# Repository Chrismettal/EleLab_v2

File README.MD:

# Elelab_v2 <!-- omit in toc -->

## Table of contents <!-- omit in toc -->

- [Buying](#buying)
- [The concept](#the-concept)
- [The PCBs](#the-pcbs)
  - [Bus100 / Bus150](#bus100--bus150)
  - [PowerFeed](#powerfeed)
  - [Frontpanel\_a](#frontpanel_a)
- [The modules](#the-modules)
  - [Supplies](#supplies)
  - [Supply from ATX/SFX](#supply-from-atxsfx)
  - [Supply from XT60/Barrel](#supply-from-xt60barrel)
  - [Supply from Meanwell PSU](#supply-from-meanwell-psu)
  - [Supply from Bosch 18 V Battery](#supply-from-bosch-18-v-battery)
  - [Lab PSU fixed](#lab-psu-fixed)
  - [Lab PSU variable](#lab-psu-variable)
  - [Oscilloscope DSO138](#oscilloscope-dso138)
  - [Resistor decade](#resistor-decade)
    - [Performance](#performance)
  - [Component tester](#component-tester)
  - [Raspberry Pi](#raspberry-pi)
  - [Display](#display)
  - [Electronic Load](#electronic-load)
  - [Signal generator](#signal-generator)
  - [Audio amplifier / signal tracer](#audio-amplifier--signal-tracer)
  - [TS100 Soldering station](#ts100-soldering-station)
- [Tips and tricks](#tips-and-tricks)

This is a low cost, modular elctronics lab system for hobbyists.
The customizable modules include fixed and variable power supplies, measurement tools, component testers and much more.
Everything in here is done with open source software, including FreeCAD for all the 3d printable files and KiCAD for the PCBs.
I have made a set of modules already and am in the process of creating many more. Raw PCB project files, Gerbers and FreeCAD projects are all uploaded here for your customizing needs, while the finished modules are uploaded to Prusaprinters. Please be sure to upload any remix you do as it might be useful for others and especially myself!

The system features a set of backpanel bus PCBs as well as panel breakout PCBs. While the backpanel bus is not neccesary, it keeps the system modular, hot swappable and tidy. You can have the gerbers manufactured for cheap at your favorite chinese PCB house or just shoot me a message. I might have spares.

Finished modules for printing yourself for any module can be found [here in the Prusaprinters collection](https://www.prusaprinters.org/social/13425-chrismettal/collections/14323).
For most of the modules a printbed of 160x160mm and 175mm of height is sufficient, but the ATX and SFX module require print bed sizes of up to 250mm width (Prusa MK2 and up dimensions). I printed all of the modules in PLA and just to speed things up i used a 0.6mm nozzle but that is not required at all.

**If you like my work please consider [supporting my caffeine addiction](https://gitlab.com/Chrismettal#donations)!**

## Buying

All PCBs as well as 3D printed parts are now stocked at Tindie!

## The concept

The system consists of 3 basic sizes of modules, 100mm, 150mm and 200mm. For the 100mm and the 150mm frame there is a backpanel bus that interconnects the modules together for power delivery. The 200mm frame uses two of the 100mm PCBs.

For the modules we usually use one of the 3 base sizes and punch holes in the upper and/or lower front panel to suit our mounting needs. This can be done in FreeCAD by modifying the BaseXXX file or a finished module that best fits your new module. Alternatively you can also just edit the .stl files in the editor of your choice.

The backpanel bus is equipped to transfer 24 V, 12 V and 5 V (and GND, duh), which we feed into the system by one of the "Supply" modules. At the moment i made an SFX-PSU supply module (supplying 12 V and 5 V) and one with a 5.5mm barrel jack and XT60 jack (Using 24 V supplies and step-down converters for 12 V and 5 V). Both of these supply modules feature the PowerFeed PCB to feed into the backpanel bus. Because 24 V is rarely needed for most of the modules, the easiest and safest way to use this system is the SFX module, which just plugs into the PowerFeed PCB.

Obviously you can just run wires between the modules and omit the backpanel bus, but it will probably make me a little sad.

If you are using the bus, individual modules just plug into each other to form a single unit. 

With 2 little printed clips you can secure the modules together so they don't seperate during the occasional earthquake or lab-ragequit.

Almost none of the 3d printable pieces require supports. The frame of each module has integrated supports at one position, that you will need to cut away after printing:

## The PCBs

All of the PCBs can be cheaply manufactured in China (trust me, it's easier and cheaper than you think) or sometimes i even have spares left, if you shoot me a message.

### Bus100 / Bus150

This is the basic backpanel bus to link individual modules together. Though optional, it greatly enhances your experience in building this system.

**Parts:**

- 2pcs 2.54mm Pinheader right angle 2x8 female
- 2pcs 2.54mm Pinheader right angle 2x8 male

### PowerFeed

This is the main infeed to connect your power supply to the backpanel bus and feed into the modules. It packs jacks to plug in your SFX supply, screw connectors for external fuses, and a breakout for the SFXs standby switch. Alternatively you could wire up your supplies directly to the spots marked as 24V, 12V and 5V respectively without using ATX connectors.

Using a PC supply, 12 V are supplied through either a 4 or 8 pin CPU header power plug. You cannot use the 8-pin GPU plug on your high end ATX PSU.

**Parts:**

- 24 Pin 4.2mm ATX Connector standing 
-  8 Pin 4.2mm ATX Connector standing
- 6pcs 5.08mm 2 Pin screw terminal (The blue cheap ones, optional though)

### Frontpanel_a

Here we have the basic front panel breakout with industry style screw-plug connectors and USB jacks. The USB Jacks have a 0805 footprint in line with the 5 V rail so you can optionally install a tiny polyfuse in there. The data lines of each USB port are broken out so you can either use it for normal data transfer, or do whatever the best quick charge port configuration on the data lines is today. (for example bridging D+ and D- to put old Android phones into quick charge mode)

**Parts:**

- 2pcs 5.08mm pcb screw terminal block 4 pin
- 2pcs standing vertical USB Ports
- 2pcs 0805 polyfuse 1.1A (Or your desired amperage)

## The modules

### Supplies

No matter what Infeed you use, you should aim for around 100 - 150 W of power in general. I use a 24 V,  150 W power supply to infeed into my system. For PC supplies you should watch for the individual rail current, as a PSU might show 5 A of 12 V, but split over 5 rails, so if you only use one rail you will only get 1 A out of your PSU.

### Supply from ATX/SFX

The easiest way to supply power to your EleLab is to use a regular ATX or SFX computer power supply. Using the PowerFeed PCB you can plug in the 24pin and 8pin connectors of your PSU directly into the backpanel bus. The module is preconfigured to use fuses for the 12 V and 5 V rails. You could install a switch for the PowerON PSU signal but i usually just bridge it completely so i switch the EleLab on and off by the main power switch on the back of the PSU.

Make sure the fan of your PSU is exposed as in the picture as not to overheat your poor PSU.

In the picture you see me build the SFX version of the module, the ATX version is printing at the time of writing this and is not tested yet.

**Parts:**

- PowerFeed PCB
- 2pcs screw in fuse holder panel mount
- SFX PSU of your choice
- 5pcs M2x8 self tapping screws

### Supply from XT60/Barrel

With this supply module you can use any external 12 V or 24 V Power supply you want. You could even plug in some batteries with the XT60 jack!
This module however needs some beefy DC-DC step-down converters to create the 5 V rail, as well as the 12 V rail if you are using a 24 V supply. 
There is a printable tray that just snaps into the bottom, capable of carrying two of these types of step down converters:

These are readily available from china for a few bucks if you search for "step-down XL4016" on ebay. XL4016 is the name of the IC but it's the closest to a part number we get.

One of the converters will be set to output 5 V and one to output 12 V, when you supply the module with 24 V DC. This will give you all 3 voltages on the backpanel bus. The modules can also be configured for current limiting, which I set to 2 A each.

**Parts:**

- PowerFeed PCB
- 3pcs screw in fuse holder panel mount
- 2pcs DC-DC Step down converters XL4016
- 9pcs M2x8 self tapping screws

### Supply from Meanwell PSU

Using the same step down converters, but this time using an internal PSU, the Meanwell module directly integrates a high quality supply into your EleLab. 
Since you will need to wire up mains voltage i can NOT show you how to do this. 
The Module uses an IEC C14 plug with integrated switch and fuse. Can't really find an exact name to google for.

The Meanwell supply should be a 24 V one, preferably the 150 W model, using the step down converters to step the voltage to 12 V and 5 V respectively.

**Parts:**

- PowerFeed PCB
- 3pcs screw in fuse holder panel mount
- 2pcs DC-DC Step down converters XL4016
- 9pcs M2x8 self tapping screws
- 4pcs M3x5 metric screws
- Meanwell RS-150-24
- IEC C14 Plug with switch and fuse

### Supply from Bosch 18 V Battery

With this module you can use your 18 V Bosch batteries to supply a portable lab system. It also uses the same step down converters for rails of 18 V - 12 V and 5 V. Additionaly you will need two locking blade edge connectors. These are widely used in the car industry for confectionable plugs. The part number I found was “8KW048056-033” for a 6.3mm blade with 2.5mm² wire capacity.

Please note that 18 V Bosch batteries do NOT have over discharge protection built into the pack and can take damage if you run them below their specified "empty" point! Always watch the meter on your battery and make sure to use them in a healthy range. 

The edge connectors are slid in from the inside of the case and lock into place.

**Hint:** see also [standalone version](https://www.prusaprinters.org/prints/109595-bosch-18-v-battery-powerbank-power-supply)

**Parts:**

- PowerFeed PCB
- 3pcs screw in fuse holder panel mount
- 2pcs DC-DC Step down converters XL4016
- 9pcs M2x8 self tapping screws
- 2pcs “8KW048056-033” connectors
- Bosch 18 V battery

### Lab PSU fixed

The first actually usable module is a power breakout for your 5 V, 12 V and optionally 24 V rails. Using cheap chinese banana jacks with 12mm OD all rails can be accessed. In the front we use the Frontpanel_a PCB to have connections beside the banana jacks. Which terminal you connect to which rail is only dependend on your preferences. Obviously make sure to not reverse polarity on the USB ports or risk frying something. 

Here you can see the spagetthi wiring behind mine:

Be sure to bend over your connectors as seen here as there is not extremely much room for the upper front panel to slide down:

The banana jacks are intentionally uncentered to make room for labeling on the left. I did not have time to create printable labels yet but i will get to it.

**Parts:**

- 12 or 18pcs banana jacks
- Bus100 PCB
- Frontpanel_a PCB
- 10pcs M2x8 self tapping screws

### Lab PSU variable

Similar to the fixed supply we use a Frontpanel_a PCB here. The two variable step down converters (ebay is your friend again, TBDnameOfStepDown) are fed by either the 24 V or 12 V rail, depending on your infeed capabilities. Under each converter i put two banana jacks as the output, but also in parallel i wire up the industrial screw-plug connectors in the front to be outputs as well. If you are feeling adventurous you can also but the USBs behind the converters, but be vary that you can potentially but up to 24 V through the USB port then if you tell the converter to do it. The USB Jack will not be a happy charging port but rather something for debugging.

**Parts:**

- 2pcs DPS30005 or similar step down converter. You can get these in all voltage ranges under different names.
- 4pcs banana jacks
- Bus100 PCB
- Frontpanel_a PCB
- 10pcs M2x8 self tapping screws

### Oscilloscope DSO138

The DSO138 is a great "Babies first oscilloscope". This super cheap thing is awesome if you don't wanna shell out serious cash if you are going to look at simple waveforms once per year and don't really care about accuracy a lot. Oftentimes i just wanna know IF something is even executing code and don't care HOW it is doing it so i often still fire up the DSO138.

You have to remove the old power jack of the DSO138 PCB and feed in power through a 13mmx19mm rocker switch out of the 12 V rail for this to fit. 4 x M3 screws with nuts fix the DSO PCB into the panel from the back. The BNC jack is also removed, a new frontpanel screw-in BNC jack is installed in the front, and wired up to where the original jack was. This is best done with a shielded cable (though i doubt you will see much difference with a DSO of this quality..)

**Parts:**

- DSO138 kit
- 12mmx19mm rocker switch
- Bus150 PCB
- 4pcs M3 screws and nuts
- 6pcs M2x8 self tapping screws

### Resistor decade

Not really needing a backpanel this can safely be placed as the last piece of the EleLab as it does not even require power. Please follow your favorite guide on how to wire up your decade.

The 2 ends of the resistor decade are wired to two banana jacks. Also i installed 2 potentiometers into the panel, giving me some more flexibility. These are also just wired straight into 3 banana connectors.

Closing this module is tricky as well. You will need to NOT snap in the decade before sliding the front panel down:

A [schematic on how to wire the KSA-2 switches](PCB_CAD/EleLab_v2_RDecSchematic/RDecSchematic/RDecSchematic.pdf) is provided in [PDF](PCB_CAD/EleLab_v2_RDecSchematic/RDecSchematic/RDecSchematic.pdf) form, as well as a [KiCAD project](PCB_CAD/EleLab_v2_RDecSchematic/../../PCB_CAD/EleLab_v2_RDecSchematic/RDecSchematic/RDecSchematic.kicad_pro).

#### Performance

The high number of switch contacts will  cause a significant resistance error in the low range of `0-100R`, but for values above `100R` the accuracy raises greatly. The bad performance of the lower values skews the full range average / median, so seperate values for different ranges are provided.

| Range      | Average Error % | Median Error % |
| ---------- | --------------- | -------------- |
| 1R - 100R  | 16.697          | 9.890          |
| 100R - 10M | -0.265          | -0.395         |
| Full range | 16.697          | 9.890          |

These raw values have been recorded with a Keysight 34461A using 4-Wire resistance measurement:

| Target [R]  | Actual [R]  | Error [R]  | Error [%] |
| ----------- | ----------- | ---------- | --------- |
| 1.000       | 2.044       | 1.044      | 104.400   |
| 2.000       | 3.016       | 1.016      | 50.800    |
| 3.000       | 4.036       | 1.036      | 34.533    |
| 4.000       | 4.992       | 0.992      | 24.800    |
| 5.000       | 5.985       | 0.985      | 19.700    |
| 6.000       | 6.986       | 0.986      | 16.433    |
| 7.000       | 7.990       | 0.990      | 14.143    |
| 8.000       | 9.024       | 1.024      | 12.800    |
| 9.000       | 10.063      | 1.063      | 11.811    |
| 10.000      | 10.989      | 0.989      | 9.890     |
| 20.000      | 20.995      | 0.995      | 4.975     |
| 30.000      | 30.974      | 0.974      | 3.247     |
| 40.000      | 40.937      | 0.937      | 2.342     |
| 50.000      | 50.910      | 0.910      | 1.820     |
| 60.000      | 60.910      | 0.910      | 1.517     |
| 70.000      | 70.869      | 0.869      | 1.241     |
| 80.000      | 80.774      | 0.774      | 0.968     |
| 90.000      | 90.730      | 0.730      | 0.811     |
| 100.000     | 101.004     | 1.004      | 1.004     |
| 200.000     | 200.762     | 0.762      | 0.381     |
| 300.000     | 300.620     | 0.620      | 0.207     |
| 400.000     | 400.670     | 0.670      | 0.168     |
| 500.000     | 500.468     | 0.468      | 0.094     |
| 600.000     | 600.120     | 0.120      | 0.020     |
| 700.000     | 699.932     | -0.068     | -0.010    |
| 800.000     | 799.801     | -0.199     | -0.025    |
| 900.000     | 899.823     | -0.177     | -0.020    |
| 1000.000    | 999.342     | -0.658     | -0.066    |
| 2000.000    | 2000.430    | 0.430      | 0.022     |
| 3000.000    | 2998.200    | -1.800     | -0.060    |
| 4000.000    | 3999.820    | -0.180     | -0.004    |
| 5000.000    | 4998.400    | -1.600     | -0.032    |
| 6000.000    | 5998.460    | -1.540     | -0.026    |
| 7000.000    | 6996.200    | -3.800     | -0.054    |
| 8000.000    | 7993.540    | -6.460     | -0.081    |
| 9000.000    | 8991.460    | -8.540     | -0.095    |
| 10000.000   | 9957.250    | -42.750    | -0.428    |
| 20000.000   | 19904.500   | -95.500    | -0.478    |
| 30000.000   | 29845.600   | -154.400   | -0.515    |
| 40000.000   | 39806.000   | -194.000   | -0.485    |
| 50000.000   | 49754.000   | -246.000   | -0.492    |
| 60000.000   | 59723.000   | -277.000   | -0.462    |
| 70000.000   | 69684.700   | -315.300   | -0.450    |
| 80000.000   | 79651.800   | -348.200   | -0.435    |
| 90000.000   | 89589.100   | -410.900   | -0.457    |
| 100000.000  | 99555.100   | -444.900   | -0.445    |
| 200000.000  | 199155.000  | -845.000   | -0.423    |
| 300000.000  | 298855.000  | -1145.000  | -0.382    |
| 400000.000  | 398422.000  | -1578.000  | -0.395    |
| 500000.000  | 498035.000  | -1965.000  | -0.393    |
| 600000.000  | 597631.000  | -2369.000  | -0.395    |
| 700000.000  | 697278.000  | -2722.000  | -0.389    |
| 800000.000  | 796824.000  | -3176.000  | -0.397    |
| 900000.000  | 896647.000  | -3353.000  | -0.373    |
| 1000000.000 | 993580.000  | -6420.000  | -0.642    |
| 2000000.000 | 1987110.000 | -12890.000 | -0.645    |
| 3000000.000 | 2979190.000 | -20810.000 | -0.694    |
| 4000000.000 | 3974220.000 | -25780.000 | -0.645    |
| 5000000.000 | 4970280.000 | -29720.000 | -0.594    |
| 6000000.000 | 5965340.000 | -34660.000 | -0.578    |
| 7000000.000 | 6958820.000 | -41180.000 | -0.588    |
| 8000000.000 | 7953500.000 | -46500.000 | -0.581    |
| 9000000.000 | 8948330.000 | -51670.000 | -0.574    |
| 9999999.000 | 9944400.000 | -55599.000 | -0.556    |

**Parts:**

- 7pcs Thumbwheel switches KSA-2 with the ending caps
- 9pcs each of 1, 10, 100, 1k, 10k, 100k and 1M Ohm reistor
- 2pcs 9mm potentiometers of your choice, i used 5K B and 25K B
- 8pcs banana jacks
- Bus100 PCB
- 4pcs M2x8 self tapping screws

### Component tester

You would not believe how much utility you will get out of these things. They are also very cheaply ordered from ebay, screw into the upper panel from the backside and can identify almost all of the components you throw at it. Usually these are fed by a 9 V battery and while you could till do that and have a battery lying inside the module i just feed it from the 12 V rail. Don't know about any longterm damages though.

I wired 3 banana jacks right to the easiest to reach points numbered 1, 2 and 3.

**Parts:**

- Component Tester module
- 3pcs banana jacks
- Bus100 PCB
- 9pcs M2x8 self tapping screws

### Raspberry Pi 

Raspberry Pi carrier with USB / Ethernet / HDMI and GPIO broken out, including HAT compatible front plate. I use a "GPIO screw terminal hat" as the front plate to easily break out all GPIOs, but still be able to connect a GPIO extension cord down to a breadboard, or stack more HATs on top.

The Pi is powered through the bottom side of the GPIO header since the top side is taken by the GPIO extension cord. 5 V from the back panel is directly applied through a rocker switch.

Make sure to plug in the GPIO extension as shown. This is basically the only way it will be long enough and also the only way where the new header in the upper panel will be right side up and not mirrored.
I recommend mounting a breakout / extension HAT as shown to have easy screw terminal access to all GPIO pins, but still be able to plug HATs on top of it. Mounting the HAT now, screwing in PCB standoffs and THEN hot-snotting the extension cord in place from the back makes mounting much easier.

You will also need an angled mini-HDMI to HDMI cable. Make sure it is angled the correct way since it won't fit otherwise.

**Parts:**

- Raspberry Pi
- HDMI Female - Female front panel connector
- GPIO extension cord male-female about 150mm
- Bus100 PCB
- 12mmx19mm rocker switch
- angled short mini-HDMI to HDMI cable
- optionally - GPIO breakout board of your choice

### Display

7 Inch HDMI Display with touchscreen. HDMI and USB broken out.

**WARNING:** currently, to use the same frontpanel, a USB-A plug is used for the touchscreen. Usually you would use a Micro USB, USB C, or USB-B header for this breakout. To actually use the touchscreen for now you would have to use an USB-A to A cable, until someone made a frontpanel for USB-C or Micro USB (might be me idk).
If you are using the Frontpanel_A be sure to NOT populate the fuse, so you disconnect the 5 V rails of both USB devices.

You will need a short angled HDMI cable and an angled USB-Micro cable like shown, as straight cables won't fit in the frame. The HDMI cable connects directly to a female-female HDMI front panel mount, while the USB cable is cut open and soldered to the Frontpanel_A.

The display is powered with 5 V through a rocker switch, soldered directly to the shown points on the board. I used the GND of one of the Micro USB plugs, and 5 V is applied to the middle of the display switch. You could also cut open a second USB cable and use that, but I did not want to waste these precious angled cables

This modules works great in conjunction with the RPi module!

**Parts:**

- Waveshare 7 inch HDMI Display C
- 2 x Bus100 PCB
- Frontpanel_A PCB with only one USB jack mounted
- 12mmx19mm rocker switch
- 8pcs M2x8 self tapping screws
- 6pcs M3x15 metric screws with nuts
- female-female HDMI front panel connector
- angled HDMI cable
- angled micro USB cable

### Electronic Load

30 W electronic load module, don't know everything it can do yet, but you'll figure it out.
This module actually uses the fan opening in the back of the frame since it does generate some heat (duh).
It does have 4 wire measurement but I chose to omit this here to avoid confusion. For loads this small and modules with this low accuracy I did not see the benefit. The 4 wire measurement is therefore connected on the inside to the 2 terminals directly:

**Parts:**

- WEL3005 or similar electronic load module
- Bus100 PCB
- Frontpanel_A PCB
- 8pcs M2x8 self tapping screws
- 30mm fan

### Signal generator

4-20mA / 2-10 V / PWM signal generator. All contacts are broken out to banana jacks as well as the front panel in the order of your choice.

**Parts:**

- WSFG-06 or similar signal generator module
- Bus100 PCB
- Frontpanel_A PCB
- 8pcs M2x8 self tapping screws

### Audio amplifier / signal tracer

Mono speaker with tiny amplifier mainly for audible signal tracing. Music won't sound good on this device so please don't expect a workshop audio system in your lab. Left and right inputs are shorted together and the right input on the PAM is pulled to GND so we only use the left input in mixed-down-mono configuration.

The speaker is only glued in to accomodate all speaker sizes, so any speaker with below around 80mm diameter will work. 3-4 W is a typical power for speakers of these sizes.

Since this device is only mono, you should connect both channels together to one PAM input. For this, use two resistors (anything between 3k3 and 10k is probably fine) as shown here.

I put the output of both resistors to both channels so it does not matter which channel I use for the speaker output. I also put some heatshrink over the two resistors for some mechanical stability.

**Parts:**

- PAM8403 amplifier module with switching pot
- Bus100 PCB
- Some speaker - 75mm outer dia in my case
- 1/4 (6.35mm) Inch stereo jack

### TS100 Soldering station

Soldering "station" for TS100 soldering irons. The Iron can be kept in an ugly holder up top, powered by the XT60 plug below. The upper front plate is done with two snap-in buckets since the buckets are too deep to be sled in from the top fully. The upper bucket is meant for a soldering sponge and the lower bucket can keep your solder wire. I would either print the upper one in something heat resistant like PC or just use some aluminium tape on the inside so you don't burn the plastic with the hot tip.

The XT60 plug is snapped in from the front after soldering some heavy wires to it. Afterwards you can solder the wires to the Bus100 PCB (24V). 

The skateboard bearing is just pressed in the top. If it's too loose you can also glue it in.

Both buckets snap in from the front as the last item.

Make sure to use this module "more to the left" of your EleLab, since it draws quite a lot of power, which you probably don't want to travel through 20 modules.

**Parts:**

- Bus100 PCB
- 608ZZ skateboard bearing for the holder
- XT60 female plug

## Tips and tricks

You can keep the wires nice and short if you put together the modules as follows:

### Wire up your frontpanels  <!-- omit in toc -->

### If your wires are long enough you can place and screw in your backpanel bus already <!-- omit in toc -->

### Slide on the UPPER PANEL FIRST but don't do it all the way yet. <!-- omit in toc -->

### Slide in the LOWER PANEL now. You will see how this requires much less wiring you need for this. <!-- omit in toc -->

### Now slide on the upper panel fully. <!-- omit in toc -->

### If you have really short cables running from your front panels to your backpanel bus you can also slide in the frontpanel first and only then screw the backpanel bus into the frame. <!-- omit in toc -->

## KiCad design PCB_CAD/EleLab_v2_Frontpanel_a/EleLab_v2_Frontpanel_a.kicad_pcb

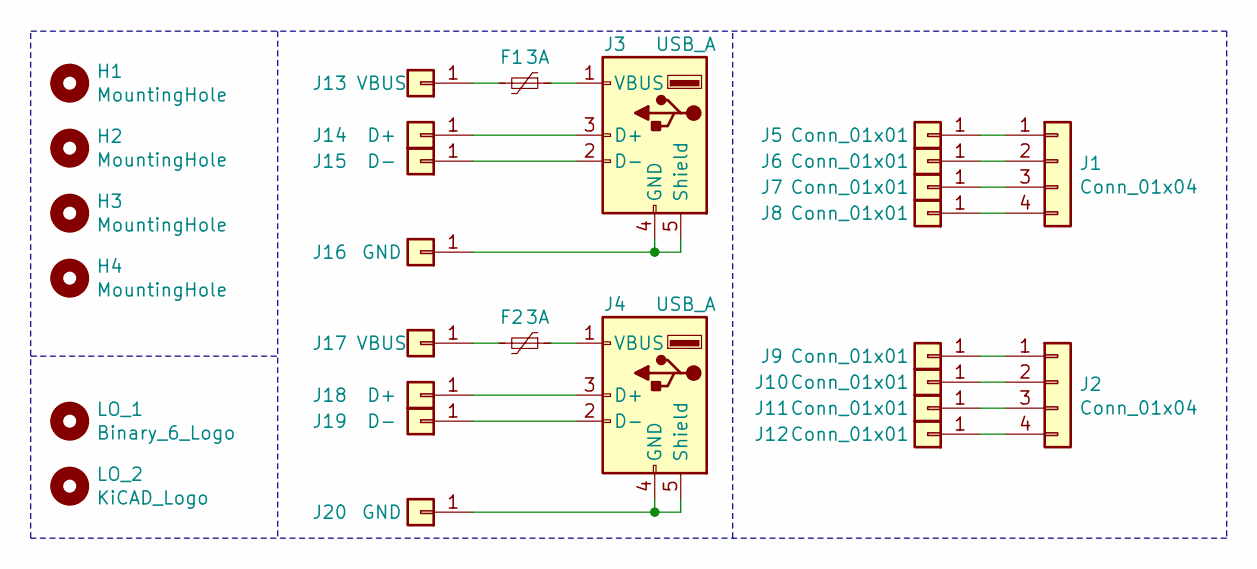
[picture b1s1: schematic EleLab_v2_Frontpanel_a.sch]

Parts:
F1, F2: 3A; Fuse_0805_2012Metric_Pad1.15x1.40mm_HandSolder
H1, H2, H3, H4: MountingHole; EigenesMountingHole_2.7mm_M2.5
J1, J2: Conn_01x04; PhoenixContact_MSTBA_2,5_4-G-5,08_1x04_P5.08mm_Horizontal
J3, J4: USB_A; USB_B_Standing
J5, J6, J7, J8, J9, J10, J11, J12: Conn_01x01; PinHeader_1x01_P2.54mm_Vertical
J13, J17: VBUS; PinHeader_1x01_P2.54mm_Vertical
J14, J18: D+; PinHeader_1x01_P2.54mm_Vertical
J15, J19: D-; PinHeader_1x01_P2.54mm_Vertical
J16, J20: GND; PinHeader_1x01_P2.54mm_Vertical
LO_1: Binary_6_Logo; Binary_6_v0.1
LO_2: KiCAD_Logo; Symbol_KiCAD-Logo_CopperAndSilkScreenTop

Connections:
unnamed: F1.1, J3.1 (VBUS)
unnamed: F1.2, J13.1
unnamed: F2.1, J4.1 (VBUS)
unnamed: F2.2, J17.1
unnamed: J1.1, J5.1
unnamed: J1.2, J6.1
unnamed: J1.3, J7.1
unnamed: J1.4, J8.1
unnamed: J2.1, J9.1
unnamed: J2.2, J10.1
unnamed: J2.3, J11.1
unnamed: J2.4, J12.1
unnamed: J3.3 (D+), J14.1
unnamed: J3.2 (D-), J15.1
unnamed: J3.4 (GND), J3.5 (Shield), J16.1
unnamed: J4.3 (D+), J18.1
unnamed: J4.2 (D-), J19.1
unnamed: J4.4 (GND), J4.5 (Shield), J20.1

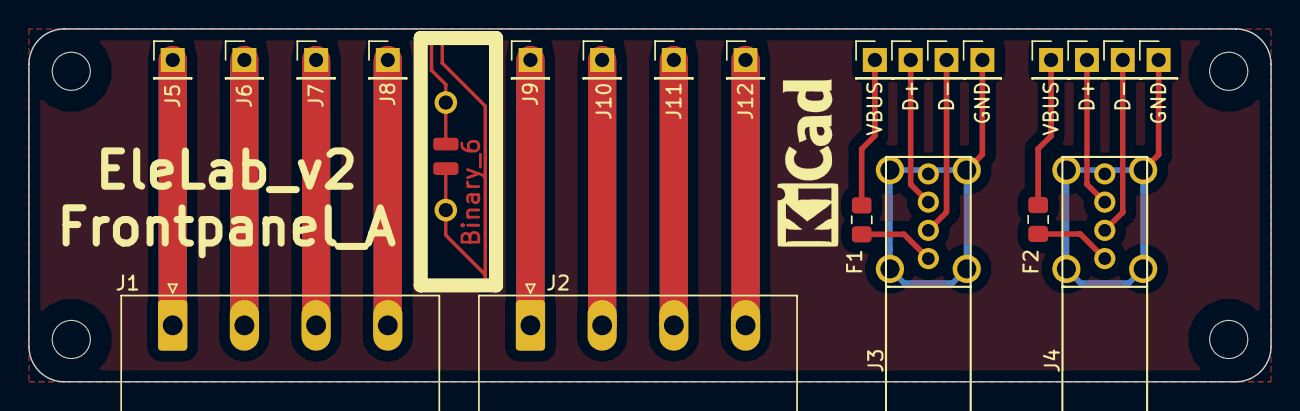
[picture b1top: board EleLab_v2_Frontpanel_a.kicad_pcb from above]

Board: 2 copper layers, 88.0 x 25.0 mm, 28 parts (0 on the bottom side), 18 nets.

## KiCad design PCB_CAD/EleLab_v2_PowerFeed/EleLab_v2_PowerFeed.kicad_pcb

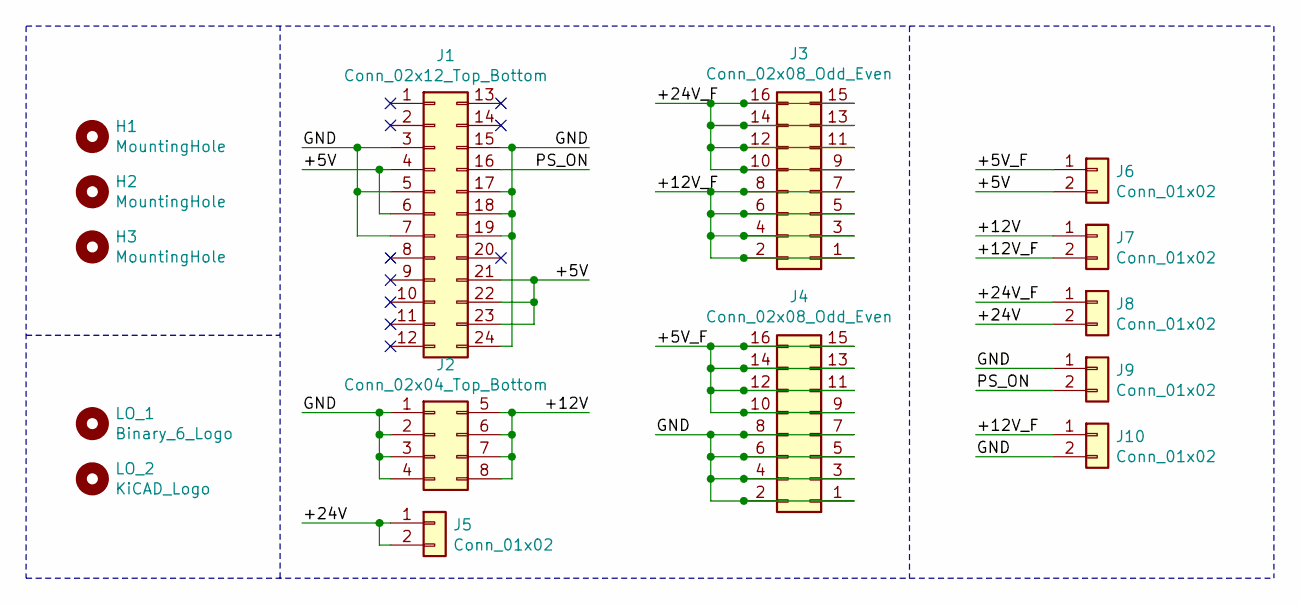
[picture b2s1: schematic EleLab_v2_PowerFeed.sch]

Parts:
H1, H2, H3: MountingHole; EigenesMountingHole_2.7mm_M2.5
J1: Conn_02x12_Top_Bottom; Molex_Mini-Fit_Jr_5566-24A_2x12_P4.20mm_Vertical
J2: Conn_02x04_Top_Bottom; Molex_Mini-Fit_Jr_5566-08A_2x04_P4.20mm_Vertical
J3, J4: Conn_02x08_Odd_Even; PinSocket_2x08_P2.54mm_Horizontal_NoSilk
J5, J6, J7, J8, J9, J10: Conn_01x02; TerminalBlock_bornier-2_P5.08mmNoSilk
LO_1: Binary_6_Logo; Binary_6_v0.1
LO_2: KiCAD_Logo; Symbol_KiCAD-Logo_CopperAndSilkScreenTop

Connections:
/+5V: J1.4, J1.6, J1.21, J1.22, J1.23, J6.2
/+5V_F: J4.9, J4.10, J4.11, J4.12, J4.13, J4.14, J4.15, J4.16, J6.1
/+12V: J2.5, J2.6, J2.7, J2.8, J7.1
/+12V_F: J3.1, J3.2, J3.3, J3.4, J3.5, J3.6, J3.7, J3.8, J7.2, J10.1
/+24V: J5.1, J5.2, J8.2
/+24V_F: J3.9, J3.10, J3.11, J3.12, J3.13, J3.14, J3.15, J3.16, J8.1
/GND: J1.3, J1.5, J1.7, J1.15, J1.17, J1.18, J1.19, J1.24, J2.1, J2.2, J2.3, J2.4, J4.1, J4.2, J4.3, J4.4, J4.5, J4.6, J4.7, J4.8, J9.1, J10.2
/PS_ON: J1.16, J9.2

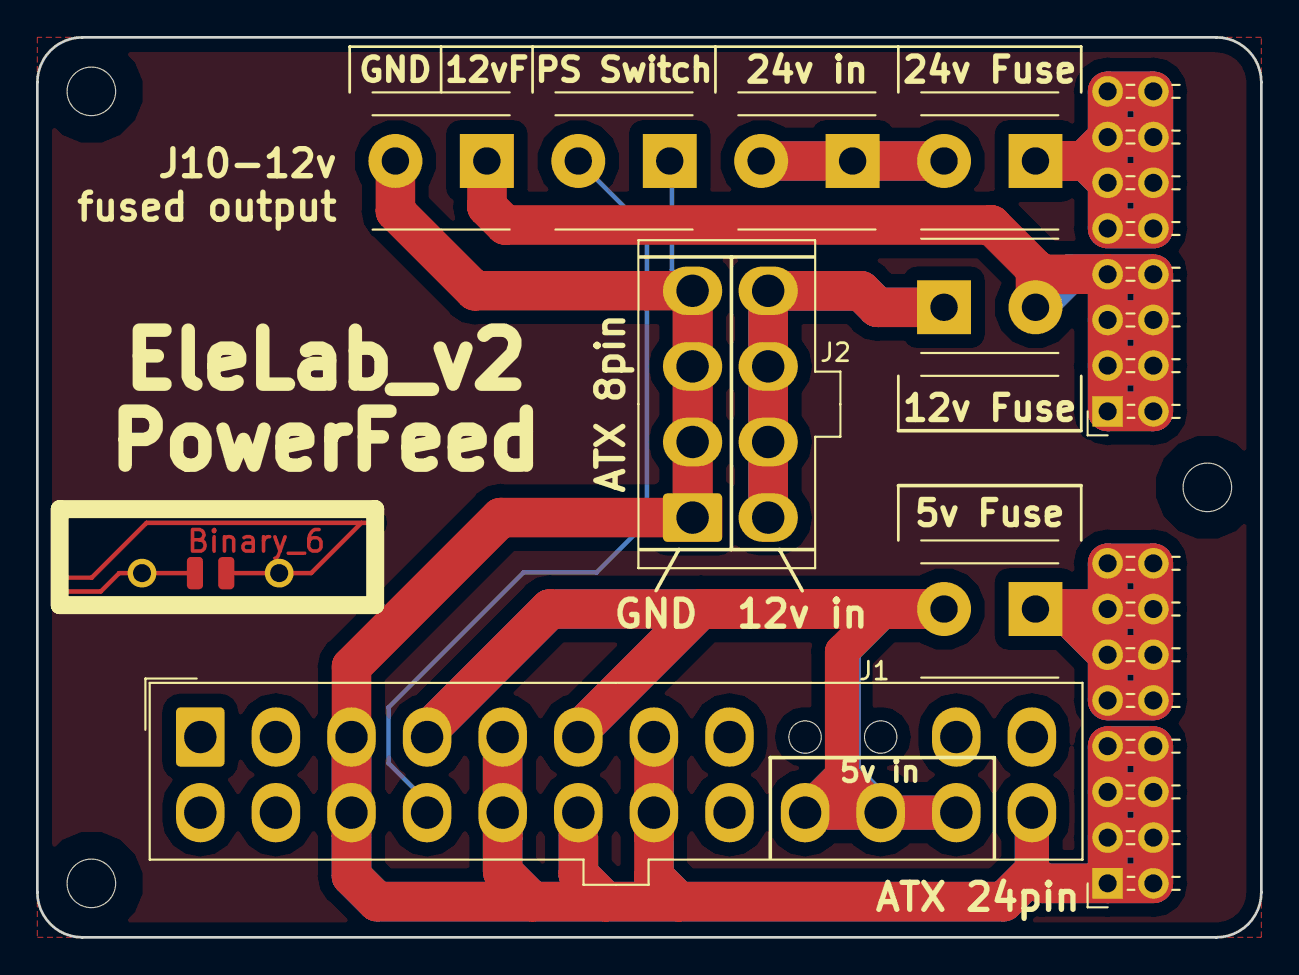
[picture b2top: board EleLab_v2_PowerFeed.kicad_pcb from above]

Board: 2 copper layers, 68.0 x 50.0 mm, 15 parts (1 on the bottom side), 8 nets.

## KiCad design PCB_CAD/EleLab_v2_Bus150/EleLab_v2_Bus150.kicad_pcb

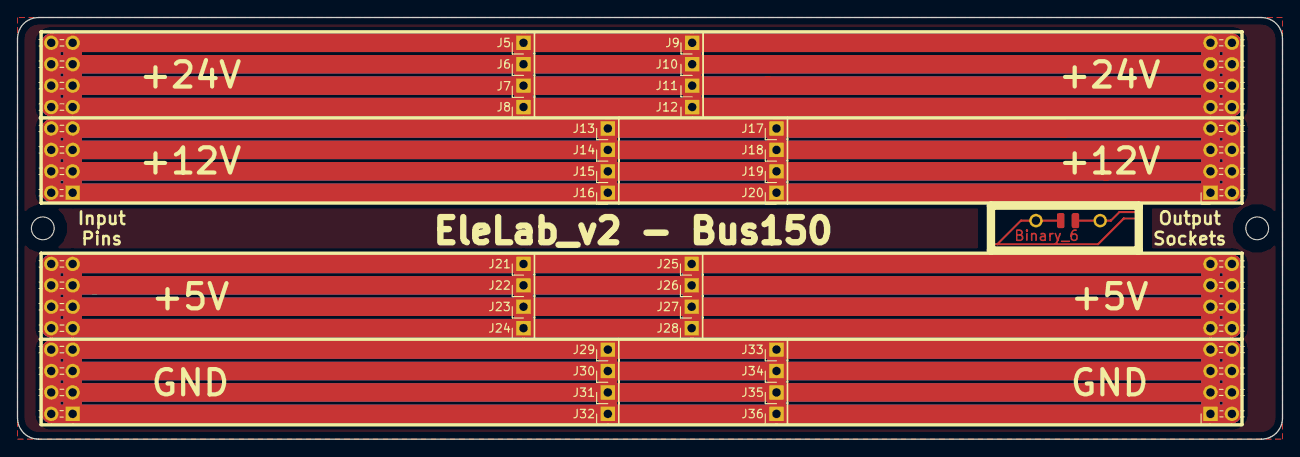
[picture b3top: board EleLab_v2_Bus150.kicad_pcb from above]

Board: 2 copper layers, 150.0 x 50.0 mm, 40 parts (1 on the bottom side), 4 nets.

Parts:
H1, H2: MountingHole; EigenesMountingHole_2.7mm_M2.5
J1, J2: Conn_02x08_Odd_Even; PinHeader_2x08_P2.54mm_Horizontal_NoSilk
J3, J4: Conn_02x08_Odd_Even; PinSocket_2x08_P2.54mm_Horizontal_NoSilk
J5, J6, J7, J8, J9, J10, J11, J12: +24 V; PinHeader_1x01_P2.54mm_Vertical
J13, J14, J15, J16, J17, J18, J19, J20: +12 V; PinHeader_1x01_P2.54mm_Vertical
J21, J22, J23, J24, J25, J26, J27, J28: +5 V; PinHeader_1x01_P2.54mm_Vertical
J29, J30, J31, J32, J33, J34, J35, J36: GND; PinHeader_1x01_P2.54mm_Vertical
LO_1: Binary_6_Logo; Binary_6_v0.1
LO_2: KiCAD_Logo; Symbol_KiCAD-Logo_CopperAndSilkScreenTop

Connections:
/+5V: J2.9, J2.10, J2.11, J2.12, J2.13, J2.14, J2.15, J2.16, J4.9, J4.10, J4.11, J4.12, J4.13, J4.14, J4.15, J4.16, J21.1, J22.1, J23.1, J24.1, J25.1, J26.1, J27.1, J28.1
/+12V: J1.1, J1.2, J1.3, J1.4, J1.5, J1.6, J1.7, J1.8, J3.1, J3.2, J3.3, J3.4, J3.5, J3.6, J3.7, J3.8, J13.1, J14.1, J15.1, J16.1, J17.1, J18.1, J19.1, J20.1
/+24V: J1.9, J1.10, J1.11, J1.12, J1.13, J1.14, J1.15, J1.16, J3.9, J3.10, J3.11, J3.12, J3.13, J3.14, J3.15, J3.16, J5.1, J6.1, J7.1, J8.1, J9.1, J10.1, J11.1, J12.1
/GND: J2.1, J2.2, J2.3, J2.4, J2.5, J2.6, J2.7, J2.8, J4.1, J4.2, J4.3, J4.4, J4.5, J4.6, J4.7, J4.8, J29.1, J30.1, J31.1, J32.1, J33.1, J34.1, J35.1, J36.1

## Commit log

2020-01-18 SFX_v1
2020-01-25 SFX_v2 - less wasted filament, some chamfers and integrated supports
2020-02-09 Removed voltage / current meters from power supply
2020-02-09 First version of 2 voltage fixed supply
2020-02-09 First version of 3 vultage supply
2020-02-09 First version of variable supply
2020-02-09 Readme test
2020-02-09 First version of XT60 / barrel jack supply
2020-02-09 First versions of DSO138 and resistor decade
2020-02-09 Remove 1 BNC from DSO138
2020-02-09 First version of component tester
2020-02-09 Edit Readme
2020-03-07 Edit CompTest - bigger hole for actuating the lever and actually fit the button.
2020-03-08 Edit DSO138 - add power switch in lower panel.
2020-03-08 Add pictures for documentation
2020-03-08 Rotate pictures
2020-03-08 Rotate moar pictures
2020-03-08 Update README for release
2020-03-09 Add parts lists to readme
2020-03-18 Finish 24v supply module
2020-05-17 Add ATX supply module
2020-05-25 Add ATX mention to readme and fix ATX screw holes
2020-05-25 Add pictures of ATX supply
2020-05-25 Edit readme with printer requirements
2020-10-13 Add FUNDING.yml
2021-06-07 Add new unfinished MW supply module
2021-06-07 Remove FreeCAD backup files
2021-06-07 Add FreeCAD backup files to gitignore
2021-06-07 Add 2 Meanwell STEP models to MW supply
2021-06-07 Remove smaller MW supply, add casing and mounting for bigger MW supply
2021-06-07 Probably finish initial version of MW supply
2021-06-07 idk tbh
2021-06-07 Add Signalgenerator module
2021-06-07 Add initial, unfinished version of Raspberry Pi module
2021-06-07 Work on RPi module. Far from finished, most measurements just guessed until material arrives
2021-06-08 Add readme information about new modules
2021-06-08 Update readme with more new module information
2021-06-08 Add unfinished version of new display module
2021-06-08 Work on display module, untested, to be measured once parts arrive
2021-06-08 Update readme with shopping information
2021-06-09 Continue working on RPi module, finish upper half
2021-06-09 Finish work on RPi module for now, waiting for parts
2021-06-09 I lied
2021-06-09 Update display module with HDMI jack
2021-06-09 Add initial version of audio amplifier module
2021-06-09 Update readme with information about even more new modules
2021-06-09 Add unfinished initial version of TS100 module
2021-06-09 Add holes for buckets to TS100 module
2021-06-09 Add upper bucket empty
2021-06-09 Add Ãlower bucket empty
2021-06-09 Rename TS100 module
2021-06-09 idktbh
2021-06-10 Fix minor measurement error in TS100 module
2021-06-10 Add upper bucket for soldering sponge
2021-06-10 Add solder holder to lower bucket
2021-06-10 Finish initial version of TS100 module - wait for printing
2021-06-10 Minor fixes in TS100 module
2021-06-10 Update readme§
2021-06-10 Rename new modules from Unfinished_
2021-06-11 Fix dimension in RPi module
2021-06-11 Align display more to the left to make room for HDMI plug
2021-06-12 Remove whatever that was
2021-06-26 Add switch to RPI module and enlarge shield hole on upper panel
2021-06-27 Remove not needed hole from Signalgenerator lower panel
2021-06-27 Add electronic load module
2021-06-27 Make all chinese insert modules like var supply tighter
2021-06-27 Update Readme with new modules
2021-06-27 Unify readme
2021-06-27 Add 30mm fan for ElectronicLoad module to readme
2021-06-27 Update readme with new pictures
2021-06-27 Add license
2021-06-28 Add Meanwell supply documentation to readme
2021-07-13 Update Readme with Prusaprinters information
2021-07-21 Update readme with PSU information
2021-07-21 Remove GitHub specific funding file
2021-08-29 Add measurements and schematic of RDec
2021-08-29 Move TOC up
2022-01-01 Start new SupplyBosch module
2022-01-03 Finish untested SupplyBosch module
2022-01-05 Add documentation of untested Bosch supply module
2022-01-05 Shameless plug
2022-01-16 Update unfinished SupplyBosch module to not fall over
2022-01-17 Add picture of mechanical testfit of BoschSupply
2022-04-22 Update Bosch picture
2022-11-19 Remove Ko-fi from readme
